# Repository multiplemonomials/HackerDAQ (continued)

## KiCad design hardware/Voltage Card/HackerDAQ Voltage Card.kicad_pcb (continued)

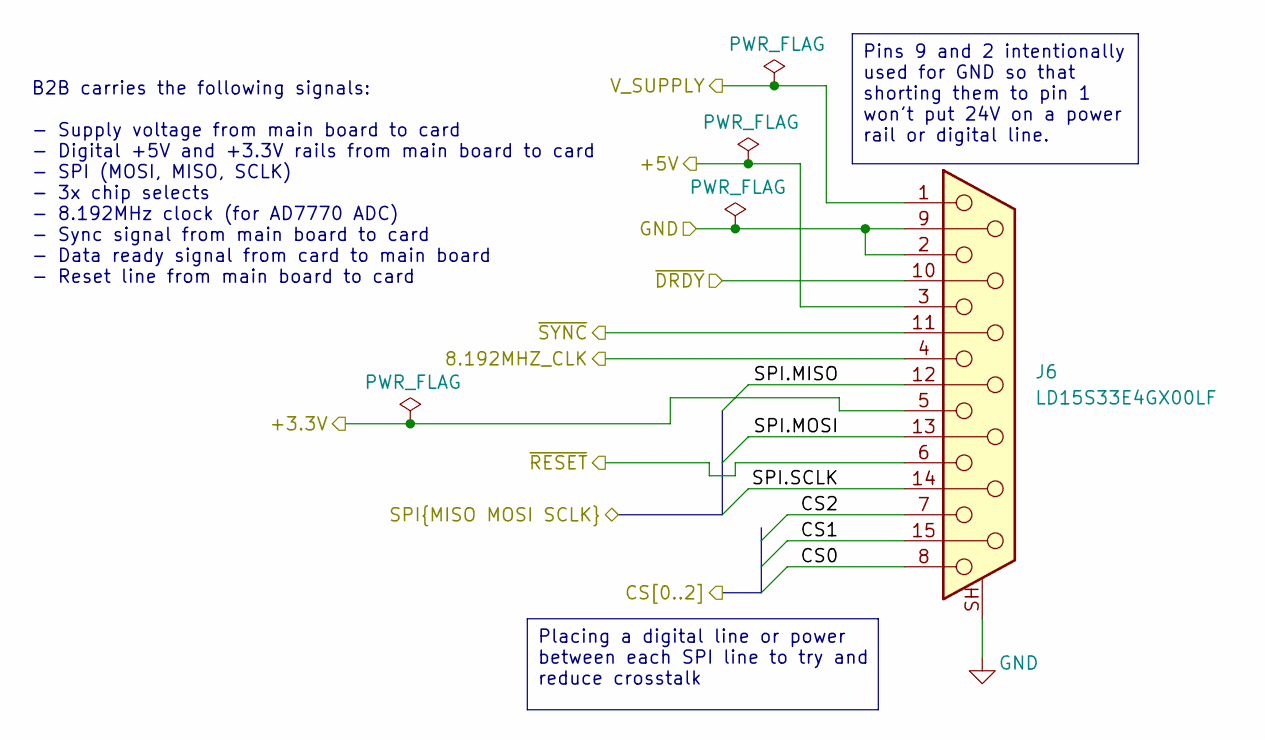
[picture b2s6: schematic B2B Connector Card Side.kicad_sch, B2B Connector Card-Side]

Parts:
J6: LD15S33E4GX00LF; Amphenol_LD15S33E4GX00LF

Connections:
+3.3V: J6.5; also elsewhere on the board
+5V: J6.3; also elsewhere on the board
+V_SUPPLY: J6.1; also elsewhere on the board
/8.192MHZ_CLK: J6.4; also elsewhere on the board
/AD7770 ADC/SPI.MISO: J6.12; also elsewhere on the board
/AD7770 ADC/SPI.MOSI: J6.13; also elsewhere on the board
/AD7770 ADC/SPI.SCLK: J6.14; also elsewhere on the board
/AD7770 ADC/~DRDY: J6.10; also elsewhere on the board
/AD7770 ADC/~RESET: J6.6; also elsewhere on the board
/AD7770 ADC/~SYNC: J6.11 (P111); also elsewhere on the board
/B2B Connector Card Side/CS0: J6.8; also elsewhere on the board
/B2B Connector Card Side/CS1: J6.15
/B2B Connector Card Side/CS2: J6.7; also elsewhere on the board
GND: J6.2, J6.9, J6.SH (PAD); also elsewhere on the board

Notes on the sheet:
B2B carries the following signals: - Supply voltage from main board to card - Digital +5V and +3.3V rails from main board to card - SPI (MOSI, MISO, SCLK) - 3x chip selects - 8.192MHz clock (for AD7770 ADC) - Sync signal from main board to card - Data ready signal from card to main board - Reset li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
Pins 9 and 2 intentionally used for GND so that shorting them to pin 1 won't put 24V on a power rail or digital line.
Placing a digital line or power between each SPI line to try and reduce crosstalk

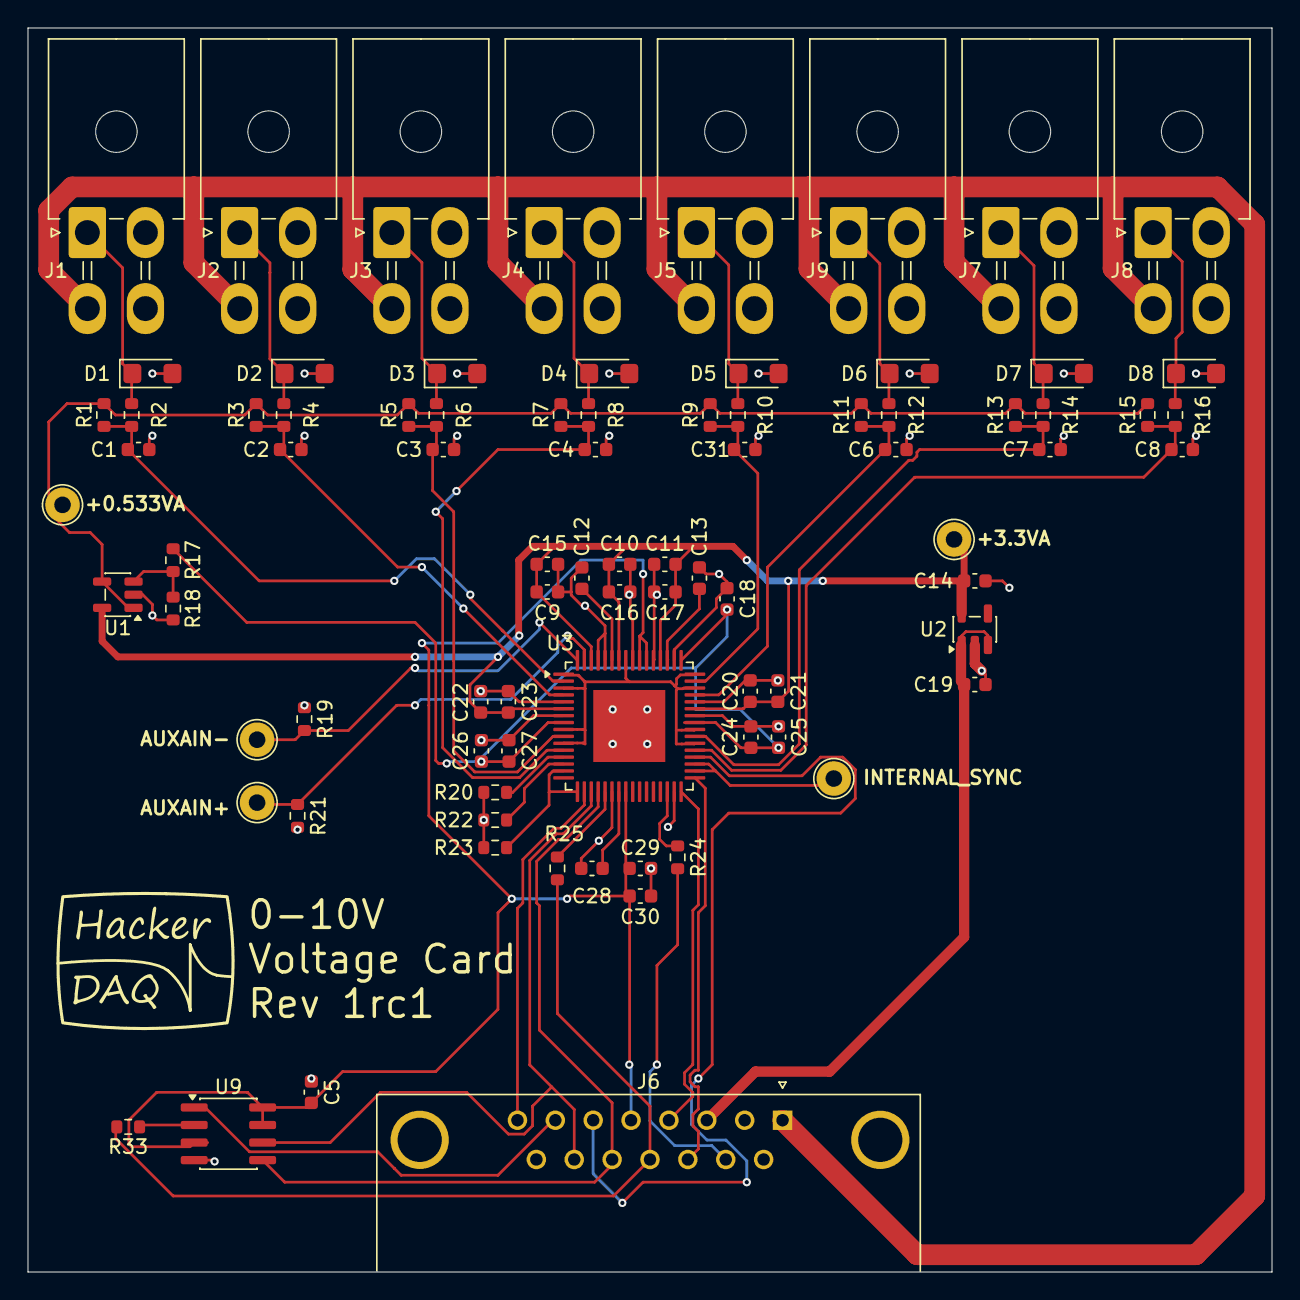
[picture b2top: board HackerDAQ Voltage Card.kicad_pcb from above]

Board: 2 copper layers, 90.0 x 90.0 mm, 92 parts (0 on the bottom side), 54 nets.

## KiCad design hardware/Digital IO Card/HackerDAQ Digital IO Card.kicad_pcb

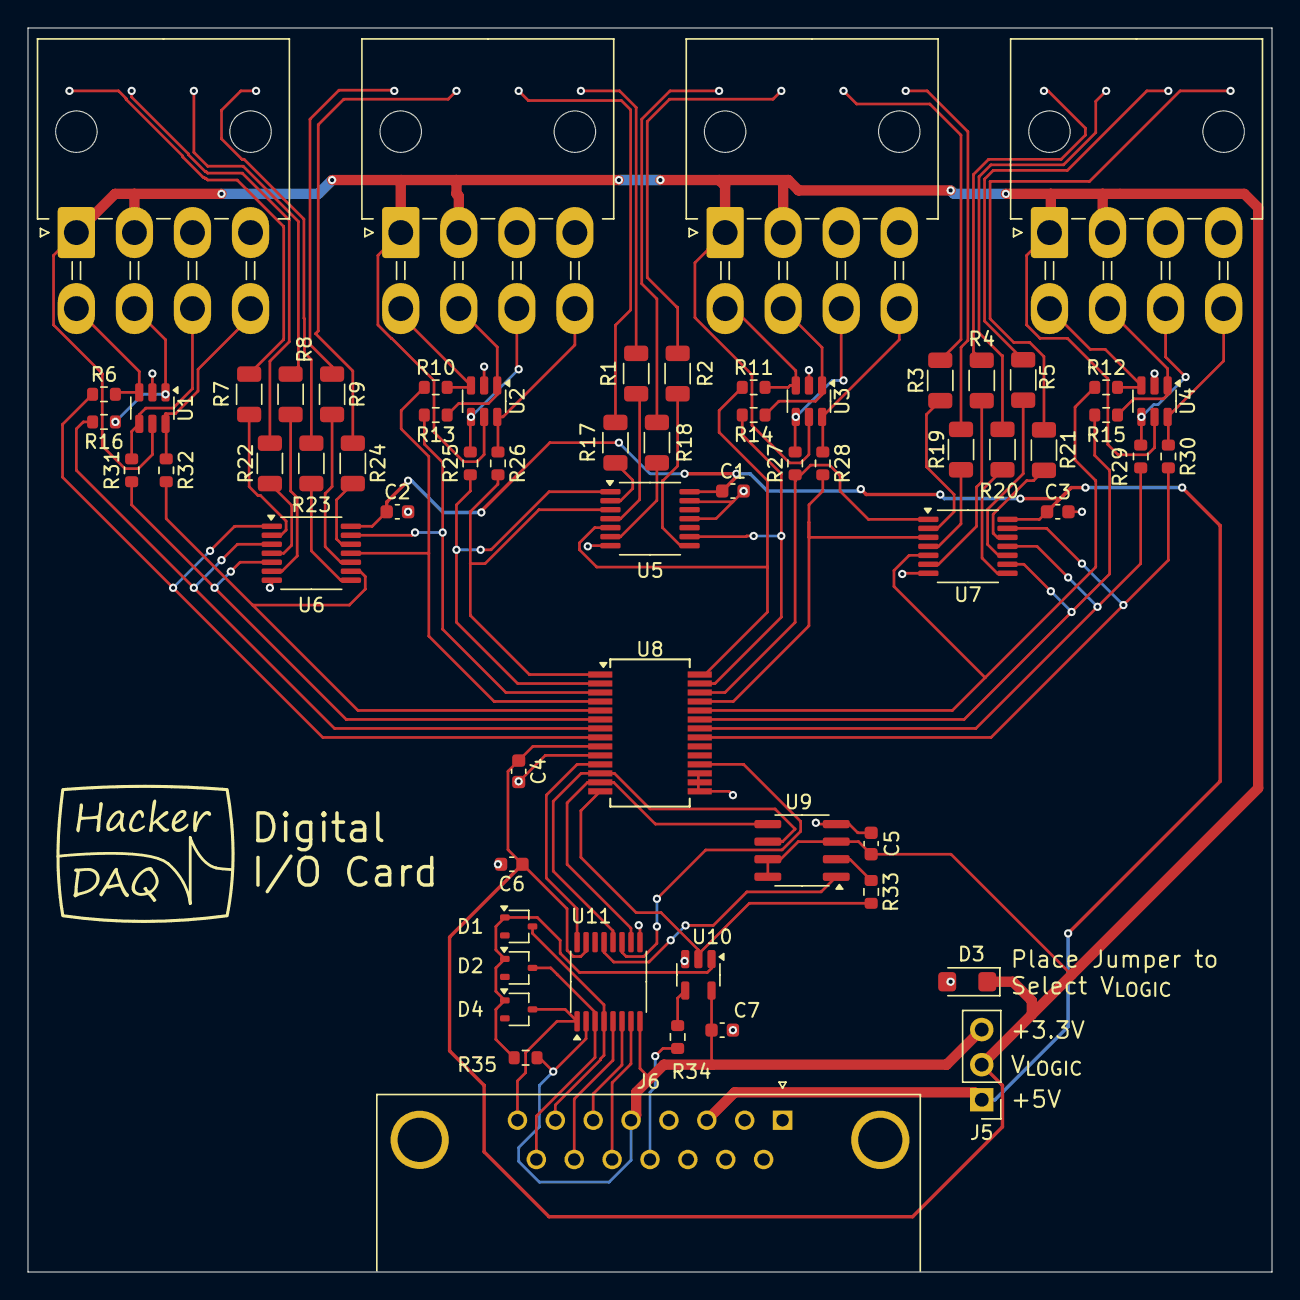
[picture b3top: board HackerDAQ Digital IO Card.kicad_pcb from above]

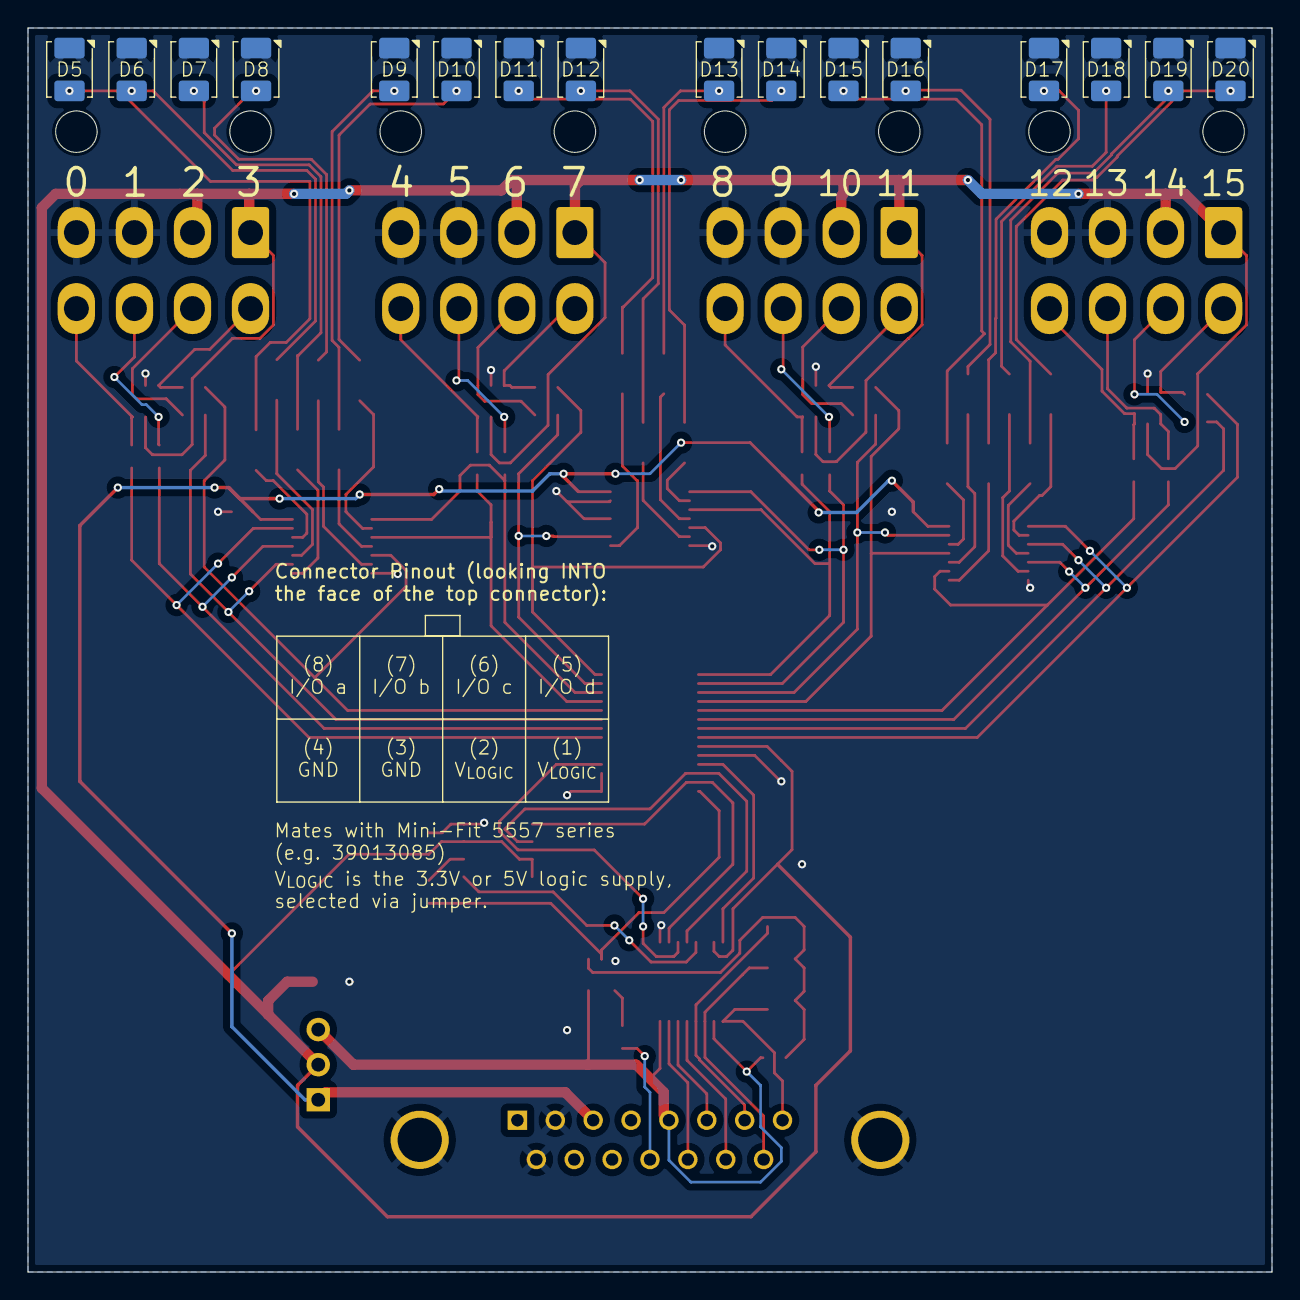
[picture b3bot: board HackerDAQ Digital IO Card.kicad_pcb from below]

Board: 2 copper layers, 90.0 x 90.0 mm, 80 parts (16 on the bottom side), 84 nets.

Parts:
C1, C2, C3, C4, C5, C6, C7: 100nF; C_0603_1608Metric
D1, D2, D4: BAT54W; SOT-323_SC-70
D3: SMF5.0A; D_SMF
D5, D6, D7, D8, D9, D10, D11, D12, D13, D14, D15, D16, D17, D18, D19, D20: AA3528SURSK; AA3528
J1, J2, J3, J4: MiniFit_Jr_5569_08A2; Molex_Mini-Fit_Jr_5569-08A2_2x04_P4.20mm_Horizontal
J5: HEADER_3x1; PinHeader_1x03_P2.54mm_Vertical
J6: LD15S33E4GX00LF; Amphenol_LD15S33E4GX00LF
LG1: HackerDAQ Logo
R1, R2, R3, R4, R5, R7, R8, R9, R17, R18, R19, R20, R21, R22, R23, R24: 150; R_1206_3216Metric
R6, R10, R11, R12, R13, R14, R15, R16, R25, R26, R27, R28, R29, R30, R31, R32, R33, R34: 33; R_0603_1608Metric
R35: 10k; R_0603_1608Metric
U1, U2, U3, U4: SRV05-4.TCT; SOT-23-6
U5, U6, U7: SN74ACT17PWR; TSSOP-14_4.4x5mm_P0.65mm
U8: MCP23S17_SS; SSOP-28_5.3x10.2mm_P0.65mm
U9: M95320-RMN6; SOIC-8_3.9x4.9mm_P1.27mm
U10: SN74AHC1G125; SOT-23-5
U11: TXB0106PW; TSSOP-16_4.4x5mm_P0.65mm

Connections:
+3.3V: C7.1, J5.3, J6.5, R35.2, U10.5 (VCC), U11.2 (V_{CCA}), U11.8 (OE)
+5V: C1.1, C2.1, C3.1, J5.1, J6.3, U5.14 (V_{CC}), U6.14 (V_{CC}), U7.14 (V_{CC})
/IO0: J4.8, R30.1, U4.6 (IO4)
/IO0_LED: R7.2, U6.2 (1Y)
/IO1: J4.7, R29.2, U4.4 (IO3)
/IO1_LED: R22.2, U6.4 (2Y)
/IO2: J4.6, R15.1, U4.1 (IO1)
/IO2_LED: R8.2, U6.6 (3Y)
/IO3: J4.5, R12.2, U4.3 (IO2)
/IO3_LED: R23.2, U6.8 (4Y)
/IO4: J3.8, R28.1, U3.6 (IO4)
/IO4_LED: R9.2, U6.10 (5Y)
/IO5: J3.7, R27.2, U3.4 (IO3)
/IO5_LED: R24.2, U6.12 (6Y)
/IO6: J3.6, R14.1, U3.1 (IO1)
/IO6_LED: R17.2, U5.2 (1Y)
/IO7: J3.5, R11.2, U3.3 (IO2)
/IO7_LED: R1.2, U5.4 (2Y)
/IO8: J2.8, R26.1, U2.6 (IO4)
/IO8_LED: R18.2, U5.6 (3Y)
/IO9: J2.7, R25.2, U2.4 (IO3)
/IO9_LED: R2.2, U5.8 (4Y)
/IO10: J2.6, R13.1, U2.1 (IO1)
/IO10_LED: R3.2, U7.2 (1Y)
/IO11: J2.5, R10.2, U2.3 (IO2)
/IO11_LED: R19.2, U7.4 (2Y)
/IO12: J1.8, R32.1, U1.6 (IO4)
/IO12_LED: R4.2, U7.6 (3Y)
/IO13: J1.7, R31.2, U1.4 (IO3)
/IO13_LED: R20.2, U7.8 (4Y)
/IO14: J1.6, R16.1, U1.1 (IO1)
/IO14_LED: R5.2, U7.10 (5Y)
/IO15: J1.5, R6.2, U1.3 (IO2)
/IO15_LED: R21.2, U7.12 (6Y)
/IOExpander/PA0: R30.2, U7.13 (6A), U8.21 (GPA0)
/IOExpander/PA1: R29.1, U7.11 (5A), U8.22 (GPA1)
/IOExpander/PA2: R15.2, U7.9 (4A), U8.23 (GPA2)
/IOExpander/PA3: R12.1, U7.5 (3A), U8.24 (GPA3)
/IOExpander/PA4: R28.2, U7.3 (2A), U8.25 (GPA4)
/IOExpander/PA5: R27.1, U7.1 (1A), U8.26 (GPA5)
/IOExpander/PA6: R14.2, U5.9 (4A), U8.27 (GPA6)
/IOExpander/PA7: R11.1, U5.5 (3A), U8.28 (GPA7)
/IOExpander/PB0: R26.2, U5.3 (2A), U8.1 (GPB0)
/IOExpander/PB1: R25.1, U5.1 (1A), U8.2 (GPB1)
/IOExpander/PB2: R13.2, U6.13 (6A), U8.3 (GPB2)
/IOExpander/PB3: R10.1, U6.11 (5A), U8.4 (GPB3)
/IOExpander/PB4: R32.2, U6.9 (4A), U8.5 (GPB4)
/IOExpander/PB5: R31.1, U6.5 (3A), U8.6 (GPB5)
/IOExpander/PB6: R16.2, U6.3 (2A), U8.7 (GPB6)
/IOExpander/PB7: R6.1, U6.1 (1A), U8.8 (GPB7)
/LevelShifter/ANY_CS_LOW: D1.1 (A), D2.1 (A), D4.1 (A), R35.1, U10.1
/SPI.MISO: J6.12, R34.1
/SPI.MOSI: J6.13, U11.7 (A6)
/SPI.SCLK: J6.14, U11.5 (A4)
/SPI_VL.MISO: R33.2, U8.14 (SO), U10.2
/SPI_VL.MOSI: U8.13 (SI), U9.5 (D), U11.10 (B6)
/SPI_VL.SCLK: U8.12 (SCK), U9.6 (C), U11.12 (B4)
/~CS_VL0: U8.11 (~CS), U11.16 (B1)
/~CS_VL2: U9.1 (~S), U11.13 (B3)
/~CS0: D4.3 (K), J6.8, U11.1 (A1)
/~CS1: D2.3 (K), J6.15, U11.3 (A2)
/~CS2: D1.3 (K), J6.7, U11.4 (A3)
/~RESET_VL: U8.18 (~RESET), U11.11 (B5)
/~RESET: J6.6, U11.6 (A5)
GND: C1.2, C2.2, C3.2, C4.2, C5.2, C6.2, C7.2, D3.2 (A2), D5.1 (K), D6.1 (K), D7.1 (K), D8.1 (K), D9.1 (K), D10.1 (K), D11.1 (K), D12.1 (K), D13.1 (K), D14.1 (K), D15.1 (K), D16.1 (K), D17.1 (K), D18.1 (K), D19.1 (K), D20.1 (K), J1.3, J1.4, J2.3, J2.4, J3.3, J3.4, J4.3, J4.4, J6.0 (PAD), J6.2, J6.9, U1.2 (VN), U2.2 (VN), U3.2 (VN), U4.2 (VN), U5.7 (GND), U5.11 (5A), U5.13 (6A), U6.7 (GND), U7.7 (GND), U8.10 (VSS), U8.15 (A0), U8.16 (A1), U8.17 (A2), U9.4 (VSS), U10.3 (GND), U11.9 (GND)
unnamed: D5.2 (A), R21.1
unnamed: D6.2 (A), R5.1
unnamed: D7.2 (A), R20.1
unnamed: D8.2 (A), R4.1
unnamed: D9.2 (A), R19.1
unnamed: D10.2 (A), R3.1
unnamed: D11.2 (A), R2.1
unnamed: D12.2 (A), R18.1
unnamed: D13.2 (A), R1.1
unnamed: D14.2 (A), R17.1
unnamed: D15.2 (A), R24.1
unnamed: D16.2 (A), R9.1
unnamed: D17.2 (A), R23.1
unnamed: D18.2 (A), R8.1
unnamed: D19.2 (A), R22.1
unnamed: D20.2 (A), R7.1
unnamed: R34.2, U10.4
unnamed: R33.1, U9.2 (Q)
V_{LOGIC}: C4.1, C5.1, C6.1, D3.1 (A1), J1.1, J1.2, J2.1, J2.2, J3.1, J3.2, J4.1, J4.2, J5.2, U1.5 (VP), U2.5 (VP), U3.5 (VP), U4.5 (VP), U8.9 (VDD), U9.3 (~W), U9.7 (~HOLD), U9.8 (VCC), U11.15 (V_{CCB})

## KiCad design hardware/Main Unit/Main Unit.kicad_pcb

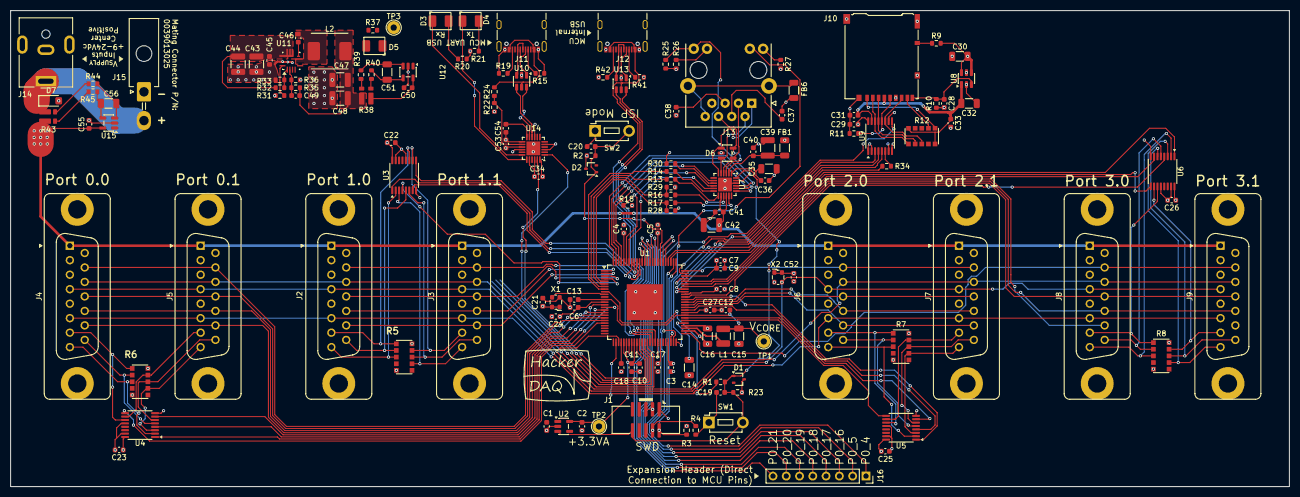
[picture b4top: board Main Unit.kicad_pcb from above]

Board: 4 copper layers, 244.5 x 91.0 mm, 151 parts (0 on the bottom side), 165 nets.

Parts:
C1, C3, C4, C5, C6, C8, C9, C11, C12, C13, C17, C19, C20, C21, C22, C23, C25, C26, C27, C33, C34, C36, C37, C38, C40, C41, C45, C46, C50, C52, C53, C55: 100nF; C_0603_1608Metric
C2, C7, C10, C24, C28, C29, C31, C54: 1µF; C_0603_1608Metric
C14, C35: 2.2µF; C_1206_3216Metric
C15, C16, C30, C32, C51, C56: 10µF; C_1206_3216Metric
C18: 220nF; C_0603_1608Metric
C39, C42, C47, C48: 22µF; C_1210_3225Metric
C43, C44: 10µF; C_1210_3225Metric
C49: 150pF; C_0603_1608Metric
D1, D2: BAT54W; SOT-323_SC-70
D3: AA3528SYSK; AA3528
D4: AA3528QBS; AA3528
D5: AA3528CGSK; AA3528
D6: ESDS304; SOT-23-5
D7: SMF24A; D_SMF
FB1, FB6: 300@100MHz; R_1206_3216Metric
J1: 3221-10-0300-00
J2, J3, J4, J5, J6, J7, J8, J9: 61801525123; Wurth_61801525123
J10: DM3AT; microSD_HC_Hirose_DM3AT-SF-PEJM5
J11, J12: USB4105-GF-A; USB_C_Receptacle_GCT_USB4105-xx-A_16P_TopMnt_Horizontal-Ext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
J13: HFJ11-2450E-L21RL; RJ45_HALO_HFJ11-x2450E-LxxRL_Horizontal-Fixed3DModel
J14: PJ-063AH; BarrelJack_CUI_PJ-063AH_Horizontal
J15: 0039300020; Molex_Mini-Fit_Jr_5569-02A2_2x01_P4.20mm_Horizontal
J16: 1x8; PinSocket_1x08_P2.54mm_Vertical
L1: 1.5µH; L_1210_3225Metric
L2: 2.2μH; 0630CDMCDDS
LG1: HackerDAQ Logo
R1, R18: 2.2k; R_0603_1608Metric
R2, R3, R4, R10, R11, R22, R23, R28, R29, R36: 10k; R_0603_1608Metric
R5, R6, R7, R8, R12: 10k; CTS 745C101
R9: 1k; R_0603_1608Metric
R13, R14, R16, R17, R34: 33; R_0603_1608Metric
R15, R19, R41, R42: 5.1k; R_0603_1608Metric
R20, R37: 140; R_0603_1608Metric
R21: 30; R_0603_1608Metric
R24, R25: 4.7k; R_0603_1608Metric
R26, R27: 270; R_0603_1608Metric
R30: 6.49k; R_0603_1608Metric
R31: 52.3k; R_0603_1608Metric
R32: 18.2k; R_0603_1608Metric
R33: 3.01k; R_0603_1608Metric
R35: 45.3k; R_0603_1608Metric
R38, R43: .0025; D1FCP0612
R39, R40, R44, R45: 10; R_0603_1608Metric
SW1, SW2: MJTP1243; SW_PUSH_1P1T_6x3.5mm_H4.3_APEM_MJTP1243
TP1: VCORE; TestPoint_THTPad_D2.5mm_Drill1.2mm
TP2: +3.3VA; TestPoint_THTPad_D2.5mm_Drill1.2mm
TP3: +3.3V; TestPoint_THTPad_D2.5mm_Drill1.2mm
U1: MCXN547VKLT; LQFP-100-1EP_14x14mm_P0.5mm_EP6.9x6.9mm_Fixed3DModel
U2: TLV71333PDBV; SOT-23-5
U3, U4, U5, U6: SN74CB3Q3257PWR; TSSOP-16_4.4x5mm_P0.65mm
U7: KSZ8081RND; QFN-24-1EP_4x4mm_P0.5mm_EP2.65x2.65mm-LengthenedPads
U8: AP22913W6-7; SOT-23-6
U9: SN74AXC4T774; TSSOP-16_4.4x5mm_P0.65mm
U10, U13: USBLC6-2SC6; SOT-23-6
U11: TPS56A37RPAR; RPA0010A-MFG
U12, U15: INA180A3; SOT-23-5
U14: CY7C65223; QFN-24-1EP_4x4mm_P0.5mm_EP2.65x2.65mm-LengthenedPads
X1: 24.0000MHz; Oscillator_SMD_ECS_2520MV-xxx-xx-4Pin_2.5x2.0mm
X2: 8.192MHz; Oscillator_SMD_ECS_2520MV-xxx-xx-4Pin_2.5x2.0mm

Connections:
+3.3V: C3.1, C4.1, C5.1, C6.1, C7.1, C8.1, C9.1, C16.2, C17.1, C21.1, C22.1, C23.1, C24.1, C25.1, C26.1, C27.1, C29.1, C30.2, C34.1, C41.1, C42.2, C50.1, C52.1, C53.1, D1.3 (K), D2.3 (K), FB1.2, J1.1, J2.5, J3.5, J4.5, J5.5, J6.5, J7.5, J8.5, J9.5, R2.2, R3.2, R5.5 (common), R5.10 (common), R6.5 (common), R6.10 (common), R7.5 (common), R7.10 (common), R8.5 (common), R8.10 (common), R9.2, R18.1, R20.1, R21.1, R23.2, R25.2, R26.2, R27.2, R37.1, R38.1, TP3.1, U1.13 (VDD/VDD_LDO_CORE/VDD_P2), U1.44 (VDD_USB), U1.47 (VDD_BAT), U1.54 (VDD_DCDC/VDD_LDO_SYS), U1.59 (VDD_P3), U1.66 (VDD_P3), U1.73 (VDD_P3), U1.83 (VDD), U1.96 (VDD), U3.16 (VCC), U4.16 (VCC), U5.16 (VCC), U6.16 (VCC), U7.14 (VDDIO), U7.16 (REF_CLK), U8.4 (VIN), U8.6 (VIN), U9.1 (DIR1), U9.2 (DIR2), U9.7 (DIR3), U9.16 (VCCA), U12.5 (V+), U14.15 (VBUS), U14.24 (VDDD), X1.1 (Tri-State), X1.4 (VDD), X2.1 (Tri-State), X2.4 (VDD)
+3.3VA: C2.1, C10.1, C11.1, TP2.1, U1.30 (VDD_ANA), U1.31 (VREFH), U1.34 (VDD_P4), U2.5 (OUT)
+5V: C1.1, J2.3, J3.3, J4.3, J5.3, J6.3, J7.3, J8.3, J9.3, U2.1 (IN)
/8.192MHZ_CLK: J2.4, J3.4, J4.4, J5.4, J6.4, J7.4, J8.4, J9.4, X2.3 (OUT)
/+3.3V_CUR_SENSE: U1.37 (P4_15), U12.1
/CARD_BUS_0_SPI.CARD_SEL: U1.15 (P2_1), U4.1 (S)
/CARD_BUS_0_SPI.MISO: J4.12, J5.12, U1.19 (P2_5)
/CARD_BUS_0_SPI.MOSI: J4.13, J5.13, U1.18 (P2_4)
/CARD_BUS_0_SPI.SCLK: J4.14, J5.14, U1.17 (P2_3)
/CARD_BUS_0_SPI.~CS0: U1.16 (P2_2), U4.4 (1A)
/CARD_BUS_0_SPI.~CS1: U1.14 (P2_0), U4.7 (2A)
/CARD_BUS_0_SPI.~CS2: U1.21 (P2_7), U4.9 (3A)
/CARD_BUS_0_SPI.~DRDY: J4.10, J5.10, U1.20 (P2_6)
/CARD_BUS_1_SPI.CARD_SEL: U1.91 (P0_23), U3.1 (S)
/CARD_BUS_1_SPI.MISO: J2.12, J3.12, U1.3 (P1_10)
/CARD_BUS_1_SPI.MOSI: J2.13, J3.13, U1.1 (P1_8)
/CARD_BUS_1_SPI.SCLK: J2.14, J3.14, U1.2 (P1_9)
/CARD_BUS_1_SPI.~CS0: U1.4 (P1_11), U3.4 (1A)
/CARD_BUS_1_SPI.~CS1: U1.90 (P0_22), U3.7 (2A)
/CARD_BUS_1_SPI.~CS2: U1.92 (P1_0), U3.9 (3A)
/CARD_BUS_1_SPI.~DRDY: J2.10, J3.10, U1.93 (P1_1)
/CARD_BUS_2_SPI.CARD_SEL: U1.64 (P3_13), U5.1 (S)
/CARD_BUS_2_SPI.MISO: J6.12, J7.12, U1.61 (P3_16)
/CARD_BUS_2_SPI.MOSI: J6.13, J7.13, U1.63 (P3_14)
/CARD_BUS_2_SPI.SCLK: J6.14, J7.14, U1.62 (P3_15)
/CARD_BUS_2_SPI.~CS0: U1.60 (P3_17), U5.4 (1A)
/CARD_BUS_2_SPI.~CS1: U1.57 (P3_20), U5.7 (2A)
/CARD_BUS_2_SPI.~CS2: U1.56 (P3_21), U5.9 (3A)
/CARD_BUS_2_SPI.~DRDY: J6.10, J7.10, U1.75 (P3_0)
/CARD_BUS_3_SPI.CARD_SEL: U1.50 (P5_2), U6.1 (S)
/CARD_BUS_3_SPI.MISO: J8.12, J9.12, U1.69 (P3_9)
/CARD_BUS_3_SPI.MOSI: J8.13, J9.13, U1.70 (P3_8)
/CARD_BUS_3_SPI.SCLK: J8.14, J9.14, U1.71 (P3_7)
/CARD_BUS_3_SPI.~CS0: U1.65 (P3_12), U6.4 (1A)
/CARD_BUS_3_SPI.~CS1: U1.78 (P0_2), U6.7 (2A)
/CARD_BUS_3_SPI.~CS2: U1.79 (P0_3), U6.9 (3A)
/CARD_BUS_3_SPI.~DRDY: J8.10, J9.10, U1.51 (P5_3)
/Card Bus Connectors0/F_CARD_CS.~CS0: J5.8, R6.2 (R2), U4.3 (1B2)
/Card Bus Connectors0/F_CARD_CS.~CS1: J5.15, R6.3 (R3), U4.6 (2B2)
/Card Bus Connectors0/F_CARD_CS.~CS2: J5.7, R6.4 (R4), U4.10 (3B2)
/Card Bus Connectors0/L_CARD_CS.~CS0: J4.8, R6.8 (R7), U4.2 (1B1)
/Card Bus Connectors0/L_CARD_CS.~CS1: J4.15, R6.7 (R6), U4.5 (2B1)
/Card Bus Connectors0/L_CARD_CS.~CS2: J4.7, R6.6 (R5), U4.11 (3B1)
/Card Bus Connectors0/~RESET: J2.6, J3.6, J4.6, J5.6, J6.6, J7.6, J8.6, J9.6, U1.27 (P4_5)
/Card Bus Connectors0/~SYNC: J2.11 (P111), J3.11 (P111), J4.11 (P111), J5.11 (P111), J6.11 (P111), J7.11 (P111), J8.11 (P111), J9.11 (P111), U1.28 (P4_6)
/Card Bus Connectors1/F_CARD_CS.~CS0: J3.8, R5.2 (R2), U3.3 (1B2)
/Card Bus Connectors1/F_CARD_CS.~CS1: J3.15, R5.3 (R3), U3.6 (2B2)
/Card Bus Connectors1/F_CARD_CS.~CS2: J3.7, R5.4 (R4), U3.10 (3B2)
/Card Bus Connectors1/L_CARD_CS.~CS0: J2.8, R5.8 (R7), U3.2 (1B1)
/Card Bus Connectors1/L_CARD_CS.~CS1: J2.15, R5.7 (R6), U3.5 (2B1)
/Card Bus Connectors1/L_CARD_CS.~CS2: J2.7, R5.6 (R5), U3.11 (3B1)
/Card Bus Connectors2/F_CARD_CS.~CS0: J7.8, R7.2 (R2), U5.3 (1B2)
/Card Bus Connectors2/F_CARD_CS.~CS1: J7.15, R7.3 (R3), U5.6 (2B2)
/Card Bus Connectors2/F_CARD_CS.~CS2: J7.7, R7.4 (R4), U5.10 (3B2)
/Card Bus Connectors2/L_CARD_CS.~CS0: J6.8, R7.8 (R7), U5.2 (1B1)
/Card Bus Connectors2/L_CARD_CS.~CS1: J6.15, R7.7 (R6), U5.5 (2B1)
/Card Bus Connectors2/L_CARD_CS.~CS2: J6.7, R7.6 (R5), U5.11 (3B1)
/Card Bus Connectors3/F_CARD_CS.~CS0: J9.8, R8.2 (R2), U6.3 (1B2)
/Card Bus Connectors3/F_CARD_CS.~CS1: J9.15, R8.3 (R3), U6.6 (2B2)
/Card Bus Connectors3/F_CARD_CS.~CS2: J9.7, R8.4 (R4), U6.10 (3B2)
/Card Bus Connectors3/L_CARD_CS.~CS0: J8.8, R8.8 (R7), U6.2 (1B1)
/Card Bus Connectors3/L_CARD_CS.~CS1: J8.15, R8.7 (R6), U6.5 (2B1)
/Card Bus Connectors3/L_CARD_CS.~CS2: J8.7, R8.6 (R5), U6.11 (3B1)
/DBG_UART.MCU_RX: U1.35 (P4_12), U14.23 (TxD)
/DBG_UART.MCU_TX: U1.36 (P4_13), U14.1 (RxD)
/DebugUSBUART/MCU_RX_LED: D3.1 (K), U14.18 (TXLED_0)
/DebugUSBUART/MCU_TX_LED: D4.1 (K), U14.19 (RXLED_0)
/DebugUSBUART/PREFILT_USBSER_D+: J11.A6 (D+), J11.B6 (D+), U10.3 (I/O2)
/DebugUSBUART/PREFILT_USBSER_D-: J11.A7 (D-), J11.B7 (D-), U10.1 (I/O1)
/DebugUSBUART/USBSER_D+: U10.4 (I/O2), U14.10 (USBDP)
/DebugUSBUART/USBSER_D-: U10.6 (I/O1), U14.11 (USBDM)
/DebugUSBUART/USBSER_VBUS: J11.A4 (VBUS), J11.A9 (VBUS), J11.B4 (VBUS), J11.B9 (VBUS), R24.2, U10.5 (VBUS)
/DebugUSBUART/USBSER_VCCD: C54.1, U14.12 (VCCD)
/DebugUSBUART/USBSER_XRES: R22.2, R24.1, U14.14 (~XRES)
/ETH_RMII.CRS_DV: R16.1, R29.2, U1.6 (P1_13)
/ETH_RMII.MDC: U1.94 (P1_2), U7.11 (MDC)
/ETH_RMII.MDIO: R18.2, U1.95 (P1_3), U7.10 (MDIO)
/ETH_RMII.RMII_CLK: U1.97 (P1_4), U7.8 (XI)
/ETH_RMII.RXD0: R13.1, U1.7 (P1_14)
/ETH_RMII.RXD1: R14.1, U1.8 (P1_15)
/ETH_RMII.RX_ER: R17.1, R28.2, U1.5 (P1_12)
/ETH_RMII.TXD0: U1.99 (P1_6), U7.20 (TXD0)
/ETH_RMII.TXD1: U1.100 (P1_7), U7.21 (TXD1)
/ETH_RMII.TX_EN: U1.98 (P1_5), U7.19 (TXEN)
/EthernetInterface/ETH_MDI_RD+: D6.4 (K), J13.3 (RD+), U7.4 (RXP)
/EthernetInterface/ETH_MDI_RD-: D6.5 (K), J13.6 (RD-), U7.3 (RXM)
/EthernetInterface/ETH_MDI_TD+: D6.1 (K), J13.1 (TD+), U7.6 (TXP)
/EthernetInterface/ETH_MDI_TD-: D6.3 (K), J13.2 (TD-), U7.5 (TXM)
/EthernetInterface/KSZ_VDD1.2: C35.1, C36.1, U7.1 (VDD_1.2)
/EthernetInterface/~LED_GREEN: J13.12, R25.1, U7.23 (LED0/ANEN_SPEED)
/MCU/CLK_24MHZ: U1.10 (EXTAL48M/P1_31), X1.3 (OUT)
/MCU/MCU_P0_4: J16.1, U1.80 (P0_4)
/MCU/MCU_P0_5: J16.2, U1.81 (P0_5)
/MCU/MCU_P0_16: J16.3, U1.84 (P0_16)
/MCU/MCU_P0_17: J16.4, U1.85 (P0_17)
/MCU/MCU_P0_18: J16.5, U1.86 (P0_18)
/MCU/MCU_P0_19: J16.6, U1.87 (P0_19)
/MCU/MCU_P0_20: J16.7, U1.88 (P0_20)
/MCU/MCU_P0_21: J16.8, U1.89 (P0_21)
/MCU/PREFILT_USBMCU_D+: J12.A6 (D+), J12.B6 (D+), U13.3 (I/O2)
/MCU/PREFILT_USBMCU_D-: J12.A7 (D-), J12.B7 (D-), U13.1 (I/O1)
/MCU/SWCLK: J1.4, R4.2, U1.77 (SWCLK/P0_1/TCLK)
/MCU/SWDIO: J1.2, R3.1, U1.76 (SWDIO/P0_0/TMS)
/MCU/USBMCU_D+: U1.40 (USB1_DP), U13.4 (I/O2)
/MCU/USBMCU_D-: U1.41 (USB1_DM), U13.6 (I/O1)
/MCU/USBMCU_VBUS: J12.A4 (VBUS), J12.A9 (VBUS), J12.B4 (VBUS), J12.B9 (VBUS), U1.42 (USB1_VBUS), U13.5 (VBUS)
/MCU/VCORE: C12.1, C13.1, C15.2, L1.2, TP1.1, U1.12 (VDD_CORE), U1.58 (VDD_CORE)
/MCU/VDD_SYS: C14.1, U1.55 (VDD_SYS)
/MCU/~ISPMODE: C20.1, D2.1 (A), R2.1, SW2.2, U1.82 (ISPMODE_N/P0_6)
/MicroSDCard/+3.3V@SD: C31.1, C32.2, C33.1, J10.4 (VDD), R12.5 (common), R12.10 (common), U8.1 (OUT), U9.15 (VCCB)
/MicroSDCard/CLK@SD: J10.5 (CLK), R11.2, U9.12 (B3)
/MicroSDCard/CMD_MOSI@SD: J10.3 (CMD), R12.2 (R2), U9.13 (B2)
/MicroSDCard/DAT0_MISO@SD: J10.7 (DAT0), R12.3 (R3), U9.11 (B4)
/MicroSDCard/DET_A: J10.10 (DET_A), R9.1
/MicroSDCard/DET_B: C28.1, J10.9 (DET_B), R10.2, U8.3 (ON)
/MicroSDCard/~CS@SD: J10.2 (DAT3/CD), R12.1 (R1), U9.14 (B1)
/SupplyTo3.3VRegulator/+3.3V_PRE_SENSE: C47.2, C48.2, C49.2, L2.2, R35.2, R38.4
/SupplyTo3.3VRegulator/BOOT: C46.1, U11.7 (BOOT)
/SupplyTo3.3VRegulator/EN: R32.1, R33.2, U11.1 (EN)
/SupplyTo3.3VRegulator/FB: C49.1, R35.1, R36.1, U11.2 (FB)
/SupplyTo3.3VRegulator/SW: C46.2, L2.1, U11.6 (SW)
/V_{SUPPLY} Input/V_{SUPPLY}_IN: D7.1 (A1), J14.1, J15.2, R43.4
/V_{SUPPLY}_CUR_SENSE: U1.39 (P4_17), U15.1
/uSD_SPI.MISO: R34.1, U1.68 (P3_10)
/uSD_SPI.MOSI: U1.74 (P3_1), U9.4 (A2)
/uSD_SPI.SCLK: U1.72 (P3_6), U9.5 (A3)
/uSD_SPI.~CS: U1.67 (P3_11), U9.3 (A1)
/~ETH_SPEED_LED: J13.10, U1.48 (P5_0)
/~MCU_RST: C19.1, D1.1 (A), J1.10, R1.1, R23.1, SW1.2, U2.3 (EN), U7.24 (~RST), U11.4 (PG)
/~SD_CARD_EN: U1.49 (P5_1), U9.9 (~OE)
GND: C1.2, C2.2, C3.2, C4.2, C5.2, C6.2, C7.2, C8.2, C9.2, C10.2, C11.2, C12.2, C13.2, C14.2, C15.1, C16.1, C17.2, C18.2, C19.2, C20.2, C21.2, C22.2, C23.2, C24.2, C25.2, C26.2, C27.2, C28.2, C29.2, C30.1, C31.2, C32.1, C33.2, C34.2, C35.2, C36.2, C37.2, C38.2, C39.1, C40.2, C41.2, C42.1, C43.1, C44.1, C45.2, C47.1, C48.1, C50.2, C52.2, C53.2, C54.2, C55.2, D5.1 (K), D6.2 (A), D7.2 (A2), FB6.2, J1.3, J1.5, J2.0 (PAD), J2.2, J2.9, J3.0 (PAD), J3.2, J3.9, J4.0 (PAD), J4.2, J4.9, J5.0 (PAD), J5.2, J5.9, J6.0 (PAD), J6.2, J6.9, J7.0 (PAD), J7.2, J7.9, J8.0 (PAD), J8.2, J8.9, J9.0 (PAD), J9.2, J9.9, J10.6 (VSS), J10.11 (SHIELD), J11.A1 (GND), J11.A12 (GND), J11.B1 (GND), J11.B12 (GND), J12.A1 (GND), J12.A12 (GND), J12.B1 (GND), J12.B12 (GND), J14.2, J15.1, R4.1, R10.1, R11.1, R15.1, R19.1, R22.1, R28.1, R29.1, R30.1, R31.1, R33.1, R36.2, R41.1, R42.1, SW1.1, SW2.1, U1.32 (VREFL), U1.33 (VSS_P4), U1.43 (VSS), U1.52 (VSS_DCDC), U1.101 (VSS), U2.2 (GND), U3.8 (GND), U3.12 (4A), U3.15 (~OE), U4.8 (GND), U4.12 (4A), U4.15 (~OE), U5.8 (GND), U5.12 (4A), U5.15 (~OE), U6.8 (GND), U6.12 (4A), U6.15 (~OE), U7.22 (GND), U7.25 (GND), U8.2 (GND), U8.5 (GND), U9.8 (DIR4), U9.10 (GND), U10.2 (GND), U11.3 (AGND), U11.9 (PGND), U12.2 (GND), U13.2 (GND), U14.3 (VSSD), U14.5 (GPIO_9), U14.9 (WAKEUP), U14.13 (VSSD), U14.16 (VSSD), U14.17 (VSSA), U14.20 (~DSR), U14.22 (~CTS), U14.25 (GND), U15.2 (GND), X1.2 (GND), X2.2 (GND)
unnamed: D3.2 (A), R20.2
unnamed: D4.2 (A), R21.2
unnamed: D5.2 (A), R37.2
unnamed: FB6.1, J13.8, J13.SH
unnamed: J10.8 (DAT1), R12.7 (R6)
unnamed: J10.1 (DAT2), R12.6 (R5)
unnamed: J11.A5 (CC1), R15.2
unnamed: J11.B5 (CC2), R19.2
unnamed: J12.A5 (CC1), R41.2
unnamed: J12.B5 (CC2), R42.2
unnamed: J13.9, R27.1
unnamed: J13.11, R26.1
unnamed: C38.1, J13.5 (RCT)
unnamed: C37.1, J13.4 (TCT)
unnamed: R38.2, R40.1
unnamed: R38.3, R39.1
unnamed: R43.2, R45.1
unnamed: R43.3, R44.1
unnamed: L1.1, U1.53 (DCDC_LX)
unnamed: C18.1, U1.29 (P4_7/VREFI/VREFO)
unnamed: R1.2, U1.9 (RESET_B)
unnamed: R16.2, U7.15 (CRS_DV/PHYAD[1:0])
unnamed: R30.2, U7.9 (REXT)
unnamed: R13.2, U7.13 (RXD0)
unnamed: R14.2, U7.12 (RXD1)
unnamed: R17.2, U7.17 (RXER)
unnamed: C39.2, C40.1, FB1.1, U7.2 (VDDA_3.3)
unnamed: R34.2, U9.6 (A4)
unnamed: R31.2, U11.10 (MODE)
unnamed: C51.2, R39.2, U12.3 (+)
unnamed: C51.1, R40.2, U12.4 (-)
unnamed: C56.2, R44.2, U15.3 (+)
unnamed: C56.1, R45.2, U15.4 (-)
V_{SUPPLY}: C43.2, C44.2, C45.1, C55.1, J2.1, J3.1, J4.1, J5.1, J6.1, J7.1, J8.1, J9.1, R32.2, R43.1, U11.8 (VIN), U15.5 (V+)

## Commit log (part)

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2026-03-01 Initial commit, nearly done with voltage card
2026-03-03 Finish initial voltage card design, add logo
2026-03-08 Start on MCU symbol and main unit
2026-03-08 Implement card connector schematic
2026-03-12 Add MicroSD card, finish MCU symbol
2026-03-14 Start on Digital IO card
2026-03-21 DIO card initial schematic done
2026-03-24 Start redoing DIO card
2026-03-25 Finish redesigned DIO card
2026-03-26 Back-annotate
2026-03-26 MCU schematic tweaks
2026-04-01 Implement Ethernet, start on voltage regulator
2026-04-01 Finish 3.3V regulator
2026-04-28 Main unit: Add USB port for MCU and 3.3VA rail, start on routing
2026-05-01 Route most of the data lines on the PCB
2026-05-03 Add schematic for Vsupply input
2026-05-07 Route more of main unit, start on KiBot CI job
2026-05-07 Missed a quote
2026-05-07 Rebuild on workflow change
2026-05-07 Extra quote
2026-05-07 Fix config path
2026-05-07 Add Main Unit to CI build as well
2026-05-07 Actually though
2026-05-07 Add Voltage Card Rev 1rc1 export
2026-05-09 Add LEDs and 5V regulator to main unit
2026-05-10 Main board routed!!
2026-05-10 Geographical reannotate
2026-05-10 Try to fix USB port model path
2026-05-10 DRC weirdness
2026-05-10 OK looks like .wrl files are not supported anymore by KiBot
2026-05-10 Release of main unit rc1!
2026-05-11 Update solder mask settings to fix PCBWay DFM issue
2026-06-22 Add Digital IO Card to CI build as well
